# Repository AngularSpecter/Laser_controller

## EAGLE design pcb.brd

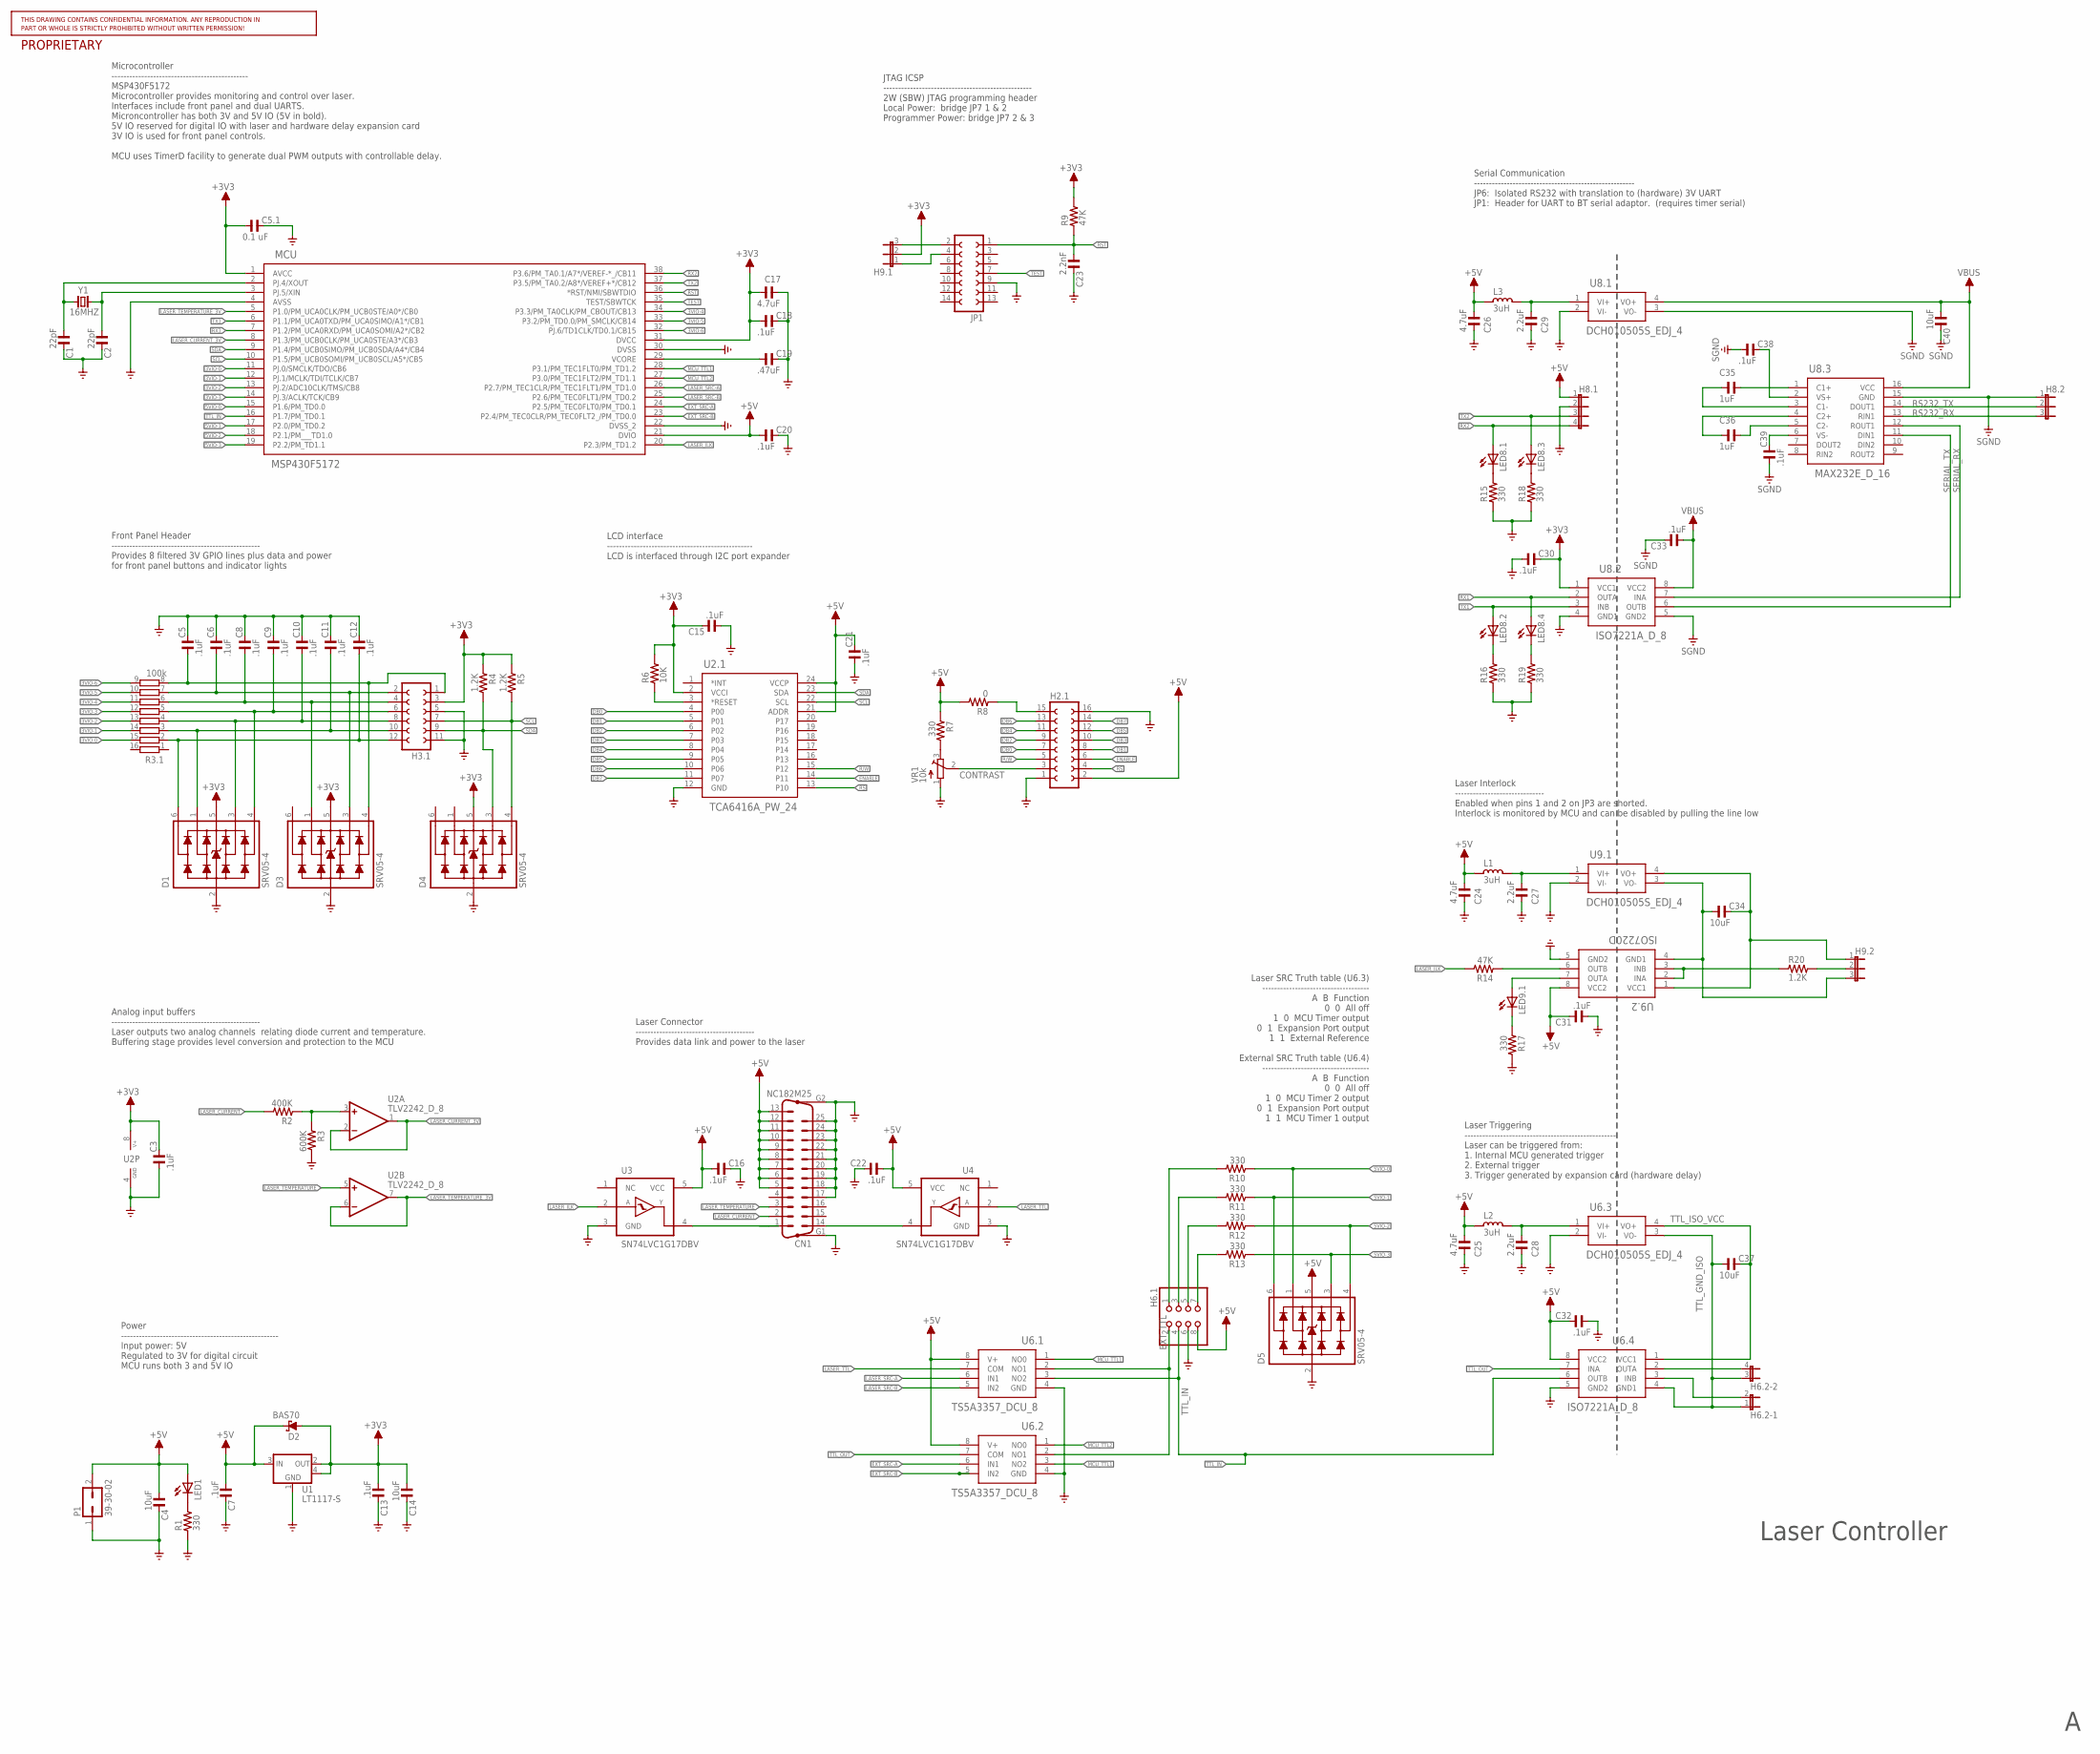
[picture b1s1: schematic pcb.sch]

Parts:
C1, C2: 22pF; C0603
C3, C5, C6, C7, C8, C9, C10, C11, C12, C13, C15, C16, C18, C20, C21, C22, C30, C31, C32, C33, C38, C39: .1uF; C0603
C4, C14, C34, C37, C40: 10uF; C0603
C5.1: 0.1 uF; C0603
C17, C24, C25, C26: 4.7uF; C0603
C19: .47uF; C0603
C23: 2.2nF; C0603
C27, C28, C29: 2.2uF; C0603
C35, C36: 1uF; C0603
CN1: NC182M25
D1, D3, D4, D5: SRV05-4; SOT23-6L
D2: BAS70; SOT23
H2.1: FE08-2
H3.1: FE06-2
H6.1: PINHD-2X4; 2X04
H6.2: JP2QE; JP2Q
H8.1: JP4E; JP4
H8.2, H9.1, H9.2: JP2E; JP2
JP1: FE07-2
L1, L2, L3: 3uH; L0805
LED1, LED8.1, LED8.2, LED8.3, LED8.4, LED9.1: LEDSMT1206; 1206
MCU: MSP430F5172; DA38
P1: 39-30-02; 39-30-?02?
R1, R7, R10, R11, R12, R13, R15, R16, R17, R18, R19: 330; R0603
R2: 400K; R0603
R3: 600K; R0603
R3.1: 100k; 2QSP16
R4, R5, R20: 1.2K; R0603
R6: 10K; R0603
R8: 0; R0603
R9, R14: 47K; R0603
U1: LT1117-S; SOT223
U2: TLV2242_D_8; SO08
U2.1: TCA6416A_PW_24; PW24
U3, U4: SN74LVC1G17DBV; SOT23-5
U6.1, U6.2: TS5A3357_DCU_8; DCU8
U6.3, U8.1, U9.1: DCH010505S_EDJ_4; EDJ4
U6.4, U8.2: ISO7221A_D_8; D8
U8.3: MAX232E_D_16; D16
U9.2: ISO7220D; D8; MANUFACTURER_PART_NUMBER iso7420_d_8
VR1: 10k; TC33X
Y1: 16MHZ; HC49/S

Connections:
3VIO-0: MCU.11 (PJ.0/SMCLK/TDO/CB6), R3.1.15
3VIO-0H: C5.1, D3.4, H3.1.1, R3.1.8
3VIO-1: MCU.12 (PJ.1/MCLK/TDI/TCLK/CB7), R3.1.14
3VIO-1H: C6.1, D3.3, H3.1.2, R3.1.7
3VIO-2: MCU.13 (PJ.2/ADC10CLK/TMS/CB8), R3.1.13
3VIO-2H: C8.1, D3.1, H3.1.4, R3.1.6
3VIO-3: MCU.14 (PJ.3/ACLK/TCK/CB9), R3.1.12
3VIO-3H: C9.1, D1.4, H3.1.6, R3.1.5
3VIO-4: MCU.34 (P3.3/PM_TA0CLK/PM_CBOUT/CB13), R3.1.11
3VIO-4H: C10.1, D1.3, H3.1.8, R3.1.4
3VIO-5: MCU.33 (P3.2/PM_TD0.0/PM_SMCLK/CB14), R3.1.10
3VIO-5H: C11.1, D1.1, H3.1.10, R3.1.3
3VIO-6: MCU.32 (PJ.6/TD1CLK/TD0.1/CB15), R3.1.9
3VIO-6H: C12.1, D1.6, H3.1.12, R3.1.2
5VIO-0: D5.1, MCU.15 (P1.6/PM_TD0.0), R10.1
5VIO-1: D5.6, MCU.17 (P2.0/PM_TD0.2), R11.1
5VIO-2: D5.4, MCU.18 (P2.1/PM___TD1.0), R12.1
5VIO-3: D5.3, MCU.19 (P2.2/PM_TD1.1), R13.1
+3V3: C3.2, C5.1.1, C13.1, C14.1, C15.2, C17.1, C18.1, C30.2, D1.5, D2.1 (A), D3.5, D4.5, H3.1.3, H9.1.2, MCU.1 (AVCC), MCU.31 (DVCC), R4.1, R5.1, R6.2, R9.2, U1.2 (OUT), U1.4 (TAB), U2.8 (V+), U2.1.2 (VCCI), U8.2.1 (VCC1)
+5V: C4.1, C7.1, C16.1, C20.1, C21.2, C22.1, C24.1, C25.1, C26.1, C31.2, C32.2, CN1.5, CN1.6, CN1.7, CN1.8, CN1.9, CN1.10, CN1.11, CN1.12, CN1.13, D2.3 (C), D5.5, H2.1.2, H6.1.8, H8.1.1, L1.2, L2.2, L3.2, LED1.A, MCU.21 (DVIO), P1.2, R7.1, R8.2, U1.3 (IN), U2.1.21 (ADDR), U2.1.24 (VCCP), U3.5 (VCC), U4.5 (VCC), U6.1.8 (V+), U6.2.8 (V+), U6.4.8 (VCC2), U9.2.8 (VCC2)
CONTRAST: H2.1.3, VR1.2 (S)
DB0: H2.1.7, U2.1.4 (P00)
DB1: H2.1.8, U2.1.5 (P01)
DB2: H2.1.9, U2.1.6 (P02)
DB3: H2.1.10, U2.1.7 (P03)
DB4: H2.1.11, U2.1.8 (P04)
DB5: H2.1.12, U2.1.9 (P05)
DB6: H2.1.13, U2.1.10 (P06)
DB7: H2.1.14, U2.1.11 (P07)
ENABLE: H2.1.6, U2.1.14 (P11)
EXT_SRC-A: MCU.24 (P2.5/PM_TEC0FLT0/PM_TD0.1), U6.2.6 (IN1)
EXT_SRC-B: MCU.23 (P2.4/PM_TEC0CLR/PM_TEC0FLT2_/PM_TD0.0), U6.2.5 (IN2)
EXT_TTL: H6.1.2, U6.1.2 (NO1), U6.2.2 (NO1)
GND: C1.2, C2.2, C3.1, C4.2, C5.2, C5.1.2, C6.2, C7.2, C8.2, C9.2, C10.2, C11.2, C12.2, C13.2, C14.2, C15.1, C16.2, C17.2, C18.2, C19.2, C20.2, C21.1, C22.2, C23.2, C24.2, C25.2, C26.2, C27.2, C28.2, C29.2, C30.1, C31.1, C32.1, CN1.17, CN1.18, CN1.19, CN1.20, CN1.21, CN1.22, CN1.23, CN1.24, CN1.25, CN1.G1, CN1.G2, D1.2, D3.2, D4.2, D5.2, H2.1.1, H2.1.16, H3.1.5, H3.1.11, H6.1.6, H8.1.2, JP1.9, MCU.4 (AVSS), MCU.22 (DVSS_2), MCU.30 (DVSS), P1.1, R1.1, R3.2, R15.1, R16.1, R17.2, R18.1, R19.1, U1.1 (GND), U2.4 (GND), U2.1.12 (GND), U3.3 (GND), U4.3 (GND), U6.1.4 (GND), U6.2.4 (GND), U6.3.2 (VI-), U6.4.5 (GND2), U8.1.2 (VI-), U8.2.4 (GND1), U9.1.2 (VI-), U9.2.5 (GND2), VR1.1 (A)
LASER_CURRENT: CN1.2, R2.2
LASER_CURRENT_3V: MCU.8 (P1.3/PM_UCB0CLK/PM_UCA0STE/A3*/CB3), U2.1 (OUT), U2.2 (-IN)
LASER_ILK: MCU.20 (P2.3/PM_TD1.2), R14.2, U3.2 (A)
LASER_ILK_HIGH: R14.1, U9.2.6 (OUTB)
LASER_SRC-A: MCU.26 (P2.7/PM_TEC1CLR/PM_TEC1FLT1/PM_TD1.0), U6.1.6 (IN1)
LASER_SRC-B: MCU.25 (P2.6/PM_TEC0FLT1/PM_TD0.2), U6.1.5 (IN2)
LASER_TEMPERATURE: CN1.3, U2.5 (+IN)
LASER_TEMPERATURE_3V: MCU.5 (P1.0/PM_UCA0CLK/PM_UCB0STE/A0*/CB0), U2.6 (-IN), U2.7 (OUT)
LASER_TTL: U4.2 (A), U6.1.7 (COM)
MCU_TTL1: MCU.28 (P3.1/PM_TEC1FLT0/PM_TD1.2), U6.1.1 (NO0), U6.2.3 (NO2)
MCU_TTL2: MCU.27 (P3.0/PM_TEC1FLT2/PM_TD1.1), U6.2.1 (NO0)
unnamed: C36.1, U8.3.4 (C2+)
unnamed: C36.2, U8.3.5 (C2-)
unnamed: C35.1, U8.3.3 (C1-)
unnamed: C35.2, U8.3.1 (C1+)
unnamed: C39.2, U8.3.6 (VS-)
unnamed: C38.2, U8.3.2 (VS+)
unnamed: LED9.1.A, U9.2.7 (OUTA)
unnamed: C27.1, L1.1, U9.1.1 (VI+)
unnamed: CN1.14, U4.4 (Y)
unnamed: H6.2.2, U6.4.3 (INB)
unnamed: CN1.1, U3.4 (Y)
unnamed: H9.1.1, JP1.4
unnamed: H9.2.2, R20.2
unnamed: R6.1, U2.1.3 (*RESET)
unnamed: H9.1.3, JP1.2
unnamed: H6.1.1, R10.2
unnamed: R2.1, R3.1, U2.3 (+IN)
unnamed: R20.1, U9.2.2 (INA), U9.2.3 (INB)
unnamed: LED1.C, R1.2
unnamed: C1.1, MCU.2 (PJ.4/XOUT), Y1.2
unnamed: C2.1, MCU.3 (PJ.5/XIN), Y1.1
unnamed: LED8.2.C, R16.2
unnamed: C19.1, MCU.29 (VCORE)
unnamed: LED8.4.C, R19.2
unnamed: LED8.1.C, R15.2
unnamed: C34.2, H9.2.1, U9.1.4 (VO+), U9.2.1 (VCC1)
unnamed: C34.1, H9.2.3, U9.1.3 (VO-), U9.2.4 (GND1)
unnamed: LED8.3.C, R18.2
unnamed: LED9.1.C, R17.1
unnamed: H6.1.3, R11.2
unnamed: C28.1, L2.1, U6.3.1 (VI+)
unnamed: C29.1, L3.1, U8.1.1 (VI+)
unnamed: H6.1.5, R12.2
unnamed: H6.1.7, R13.2
unnamed: R7.2, VR1.3 (E)
unnamed: H2.1.15, R8.1
R/W: H2.1.5, U2.1.15 (P12)
RS: H2.1.4, U2.1.13 (P10)
RS232_RX: H8.2.3, U8.3.13 (RIN1)
RS232_TX: H8.2.2, U8.3.14 (DOUT1)
RST: C23.1, JP1.1, MCU.36 (*RST/NMI/SBWTDIO), R9.1
RX1: LED8.4.A, MCU.7 (P1.2/PM_UCA0RXD/PM_UCA0SOMI/A2*/CB2), U8.2.2 (OUTA)
RX2: H8.1.4, LED8.1.A, MCU.38 (P3.6/PM_TA0.1/A7*/VEREF-*_/CB11)
SCL: D4.4, H3.1.7, MCU.10 (P1.5/PM_UCB0SOMI/PM_UCB0SCL/A5*/CB5), R5.2, U2.1.22 (SCL)
SDA: D4.3, H3.1.9, MCU.9 (P1.4/PM_UCB0SIMO/PM_UCB0SDA/A4*/CB4), R4.2, U2.1.23 (SDA)
SERIAL_RX: U8.2.7 (INA), U8.3.12 (ROUT1)
SERIAL_TX: U8.2.6 (OUTB), U8.3.11 (DIN1)
SGND: C33.2, C38.1, C39.1, C40.2, H8.2.1, U8.1.3 (VO-), U8.2.5 (GND2), U8.3.15 (GND)
TEST: JP1.7, MCU.35 (TEST/SBWTCK)
TTL_GND_ISO: C37.1, H6.2.1, H6.2.3 (1), U6.3.3 (VO-), U6.4.4 (GND1)
TTL_IN: H6.1.4, MCU.16 (P1.7/PM_TD0.1), U6.1.3 (NO2), U6.4.6 (OUTB)
TTL_ISO_VCC: C37.2, U6.3.4 (VO+), U6.4.1 (VCC1)
TTL_OUT: U6.2.7 (COM), U6.4.7 (INA)
TTL_OUT_ISO: H6.2.4 (2), U6.4.2 (OUTA)
TX1: LED8.2.A, MCU.6 (P1.1/PM_UCA0TXD/PM_UCA0SIMO/A1*/CB1), U8.2.3 (INB)
TX2: H8.1.3, LED8.3.A, MCU.37 (P3.5/PM_TA0.2/A8*/VEREF+*/CB12)
VBUS: C33.1, C40.1, U8.1.4 (VO+), U8.2.8 (VCC2), U8.3.16 (VCC)

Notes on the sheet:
Laser Interlock ------------------------------ Enabled when pins 1 and 2 on JP3 are shorted. Interlock is monitored by MCU and can be disabled by pulling the line low
Laser SRC Truth table (U6.3) ------------------------------------ A B Function 0 0 All off 1 0 MCU Timer output 0 1 Expansion Port output 1 1 External Reference External SRC Truth table (U6.4) ------------------------------------ A B Function 0 0 All off 1 0 MCU Timer 2 output 0 1 Expansion Port ou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
Serial Communication ------------------------------------------------------ JP6: Isolated RS232 with translation to (hardware) 3V UART JP1: Header for UART to BT serial adaptor. (requires timer serial)
Power ----------------------------------------------------- Input power: 5V Regulated to 3V for digital circuit MCU runs both 3 and 5V IO
Analog input buffers -------------------------------------------------- Laser outputs two analog channels relating diode current and temperature. Buffering stage provides level conversion and protection to the MCU
Laser Connector ---------------------------------------- Provides data link and power to the laser
LCD interface ------------------------------------------------- LCD is interfaced through I2C port expander
Front Panel Header -------------------------------------------------- Provides 8 filtered 3V GPIO lines plus data and power for front panel buttons and indicator lights
Laser Triggering --------------------------------------------------- Laser can be triggered from: 1. Internal MCU generated trigger 2. External trigger 3. Trigger generated by expansion card (hardware delay)
JTAG ICSP -------------------------------------------------- 2W (SBW) JTAG programming header Local Power: bridge JP7 1 & 2 Programmer Power: bridge JP7 2 & 3
Microcontroller ---------------------------------------------- MSP430F5172 Microcontroller provides monitoring and control over laser. Interfaces include front panel and dual UARTS. Microncontroller has both 3V and 5V IO (5V in bold). 5V IO reserved for digital IO with laser and hardware delay expa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
Laser Controller

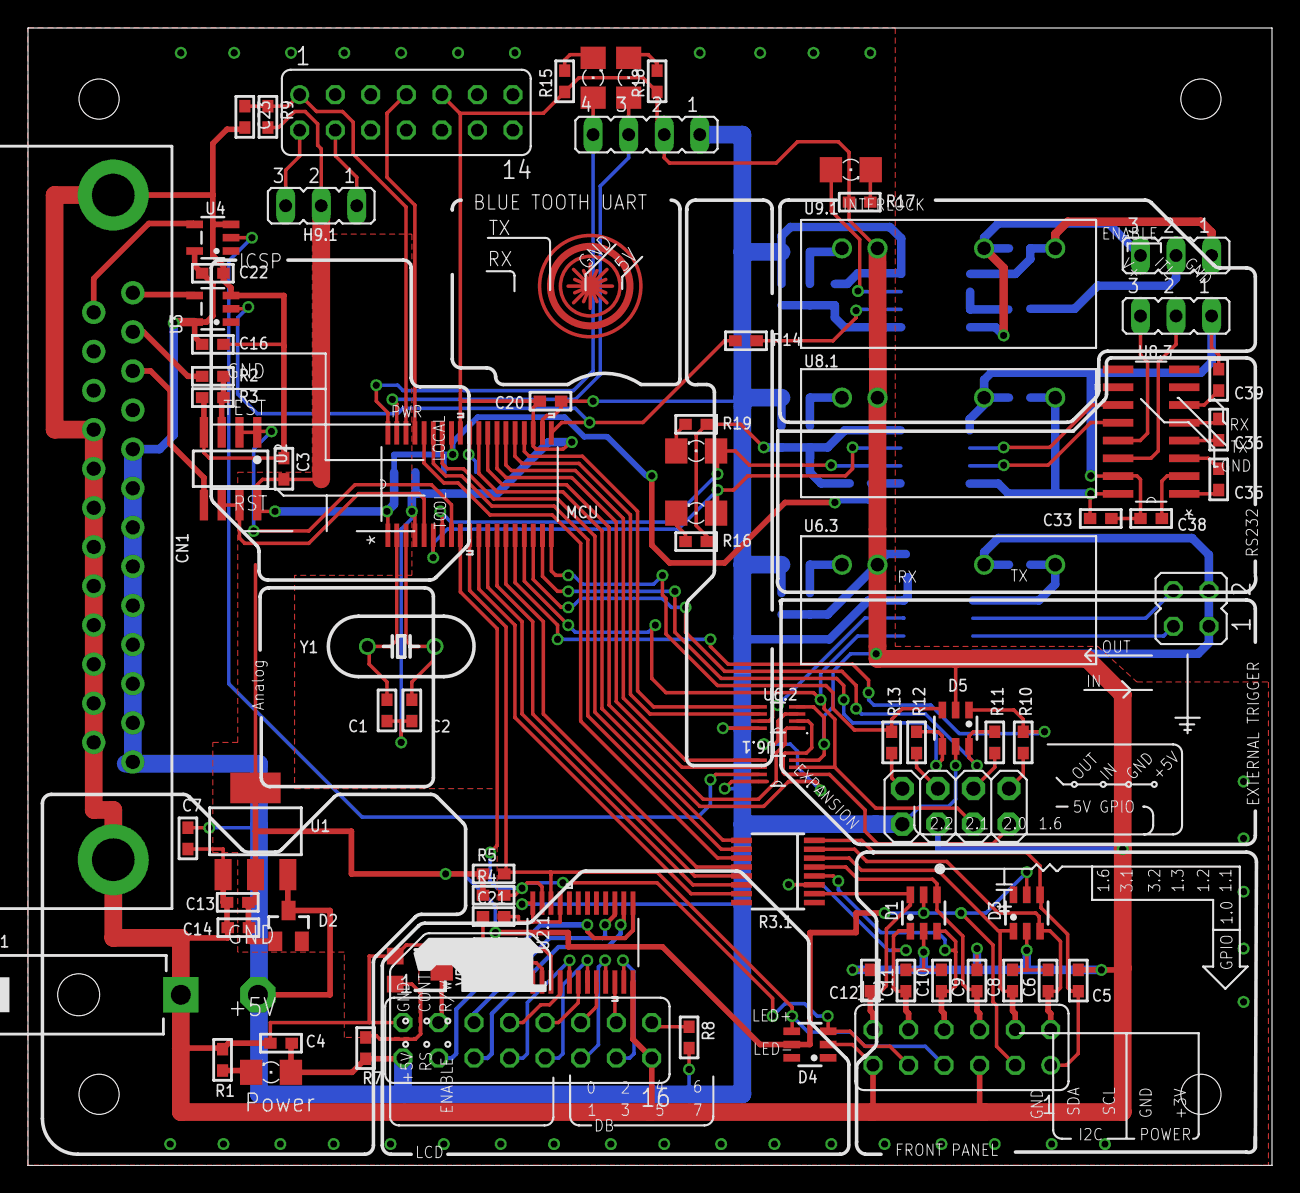
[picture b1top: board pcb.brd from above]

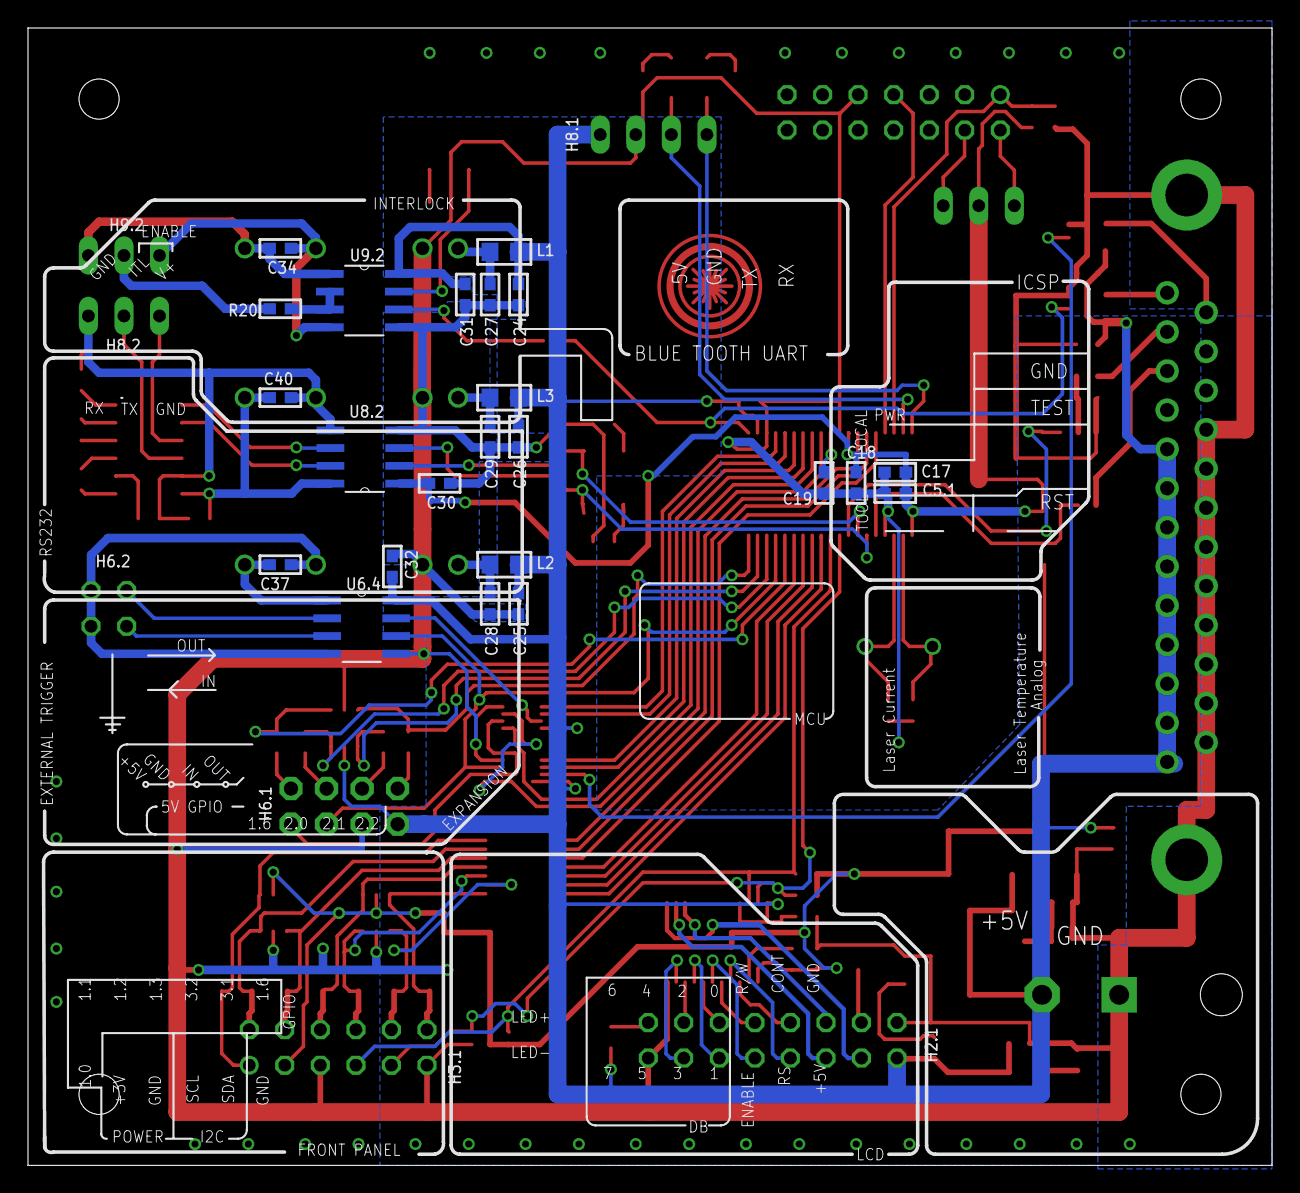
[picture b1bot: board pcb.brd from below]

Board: 2 copper layers, 88.9 x 81.3 mm, 104 parts (23 on the bottom side), 102 nets.

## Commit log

2013-03-11 Updated UART and expansion plug
    Moved to true dual UART (one timer based)
    Added remaining unused pins to expansion plug
    finished first draft routing...no DRC check
2013-03-22 updated layout and board
    Fixed interlock design
    Added analog front end to analog inputs
    changed MCU to MSP450 5 series
2013-04-10 Silk Screen and analog front end
    Update to documentation on silk screen
    Addition of buffered voltage divider for analog front end
2013-04-11 Extensive Silkscreen update, LEDS
    Added power, rx and tx LEDs
    Updates silk screen documentation
2013-04-11 Silk updates
2013-04-11 Silk screen updates
2013-04-11 Silk update
2013-04-12 Separated Analog ground from digital ground
2013-04-12 Analog ground isolation
    Moved opamp to Agnd
    added Agnd plane
    Added decoupling cap to opamp
2013-04-18 Updated Schematic.
    Updated schematic layout. Added frame, updated passive components, set
    (some) resistor values.
2013-04-19 Reliability Changes
    Changed oscillator circuit, changed voltage regulator to larger package
    (current capability), added TVS diodes and current limiting resistors to
    I/O. Updated schematic layout.
2013-04-20 Connector Update
    Added DB25 laser connector and replaced power connector with mini-fit
    Jr. Added logic buffer to laser outputs. Minor additional updates.
2013-04-22 Routing complete
    All placement complete and signals routed. Awaiting copper planes,
    renaming components, name placement and silkscreen.
2013-04-22 Copper Pours & Component Silk Complete
    Poured Copper planes and adjusted component designators for proper
    silkscreen printing. Renumbered components.
2013-04-22 Moved solder mask for logo
2013-05-14 Production Boards
    Boards as sent for production. Added BOM.
2013-05-15 Added CCS Workspace
    Added Code workspace. Setup MSP430 Project with driver library. Started
    framework for delay line: ~25% complete.
2013-05-16 Minor Changes
    Updated the proper CCR for the compare output in the delay generator.
    Setting up for PWM test output. Device clocks need to be configured
    first.
2013-05-17 Clocking, Delay Line and Signal Multiplexing
    Configured Clocks, added support for signal multiplexing and continued
    with development of the delay line.
2013-05-20 Delay Function Complete, Circular Buffers and IO Expander
    Completed the delay line functionality. Completed Circular Buffer (for
    communications), IO Expander driver partially complete.
2013-05-21 IO Expander, Laser Interface
    Completed the I/O expander functionality. Added an interface to the
    laser current, temperature and interlock functions.
2013-05-22 UART
    Completed UART driver code.
2013-05-23 Partial LCD Driver
    LCD driver is partially complete, undergoing debug.
2013-05-25 LCD Driver
    LCD Driver completed.
2013-05-27 Application Logic / Command handler
    Added RS-232 command processor and basic command handlers. Updated
    buffer and trigger delay code to accommodate the new command handlers.
    Added debug functionality to UART for test purposes.
2013-05-27 Command handlers
    Added additional command handlers, changed to string parameters in place
    of numeric parameters for future laser signal routing commands.
2013-05-27 Delay system Bug Fixes
    Updated the delay system with several bug fixes and updates.
2013-05-27 Timekeeping library
    Added Tick Timekeeping library.
2013-05-27 TICK & Front Panel UI
    Updated TICK library and added front panel UI to the LCD.
2013-05-30 Updated Delay System
    Update the trigger system to include internally generated trigger
    signals. Added application logic to support the new trigger system.
2013-06-03 Update to application code
    Fixed minor bugs in application code.
2013-06-10 Adding Labview control
2013-06-10 Updates to firmware
    1. Changing trigger mode changes signalmux
    2. External triggering with delay=0 switches mux to straight through
    3. Added interlock override
    4. disableTrigger disconnects at mux and disables timers
    5. setPeriod modified to not allow a period shorter than pulse width
    6. Added conversion routines for ADC values...currently unimplemented
2013-07-03 Updated Default delay times
    Changed default delays and added definitions for timespans.
2013-07-03 Updated Command Parser
    Created a new command parser that now accepts multiple commands in one
    string (ie :temp:triggerPeriod=200;).
2013-07-09 Updated Project Structure
    Issues with the CCS project have been repaired.
2013-07-09 Project File Update
2013-07-09 Added Project Files
2013-07-23 Set default mode to External Trigger
    Set the default triggering mode to DELAYED_TRIGGER.
2013-07-23 Fixed Bug in Laser override
2013-07-23 Updated signal chain calls.
    Changed the names to correct errors.

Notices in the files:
parts and their libraries:
rc-master-smd: Copyright (C) 2007-2008, Bob Starr
op-amp: Copyright (C) 2008, Bob Starr
con-molex-mini-fit: Copyright (C) 2011, Bob Starr
supply4: Copyright (C) 2007, Bob Starr
